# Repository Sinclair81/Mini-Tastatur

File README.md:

# Mini-Tastatur

<!-- markdownlint-disable MD033 -->

<!-- markdownlint-enable MD033 -->

A smal clone of the [Adafruit MacroPad RP2040](https://learn.adafruit.com/adafruit-macropad-rp2040).  

- Raspberry Pi Pico
- I2C Display
- 9 Buttons

[CircuitPython for Raspberry Pi Pico](https://circuitpython.org/board/raspberry_pi_pico)

[MacroPad CircuitPython Library](https://learn.adafruit.com/adafruit-macropad-rp2040/macropad-circuitpython-library)

Extract the zip and navigate to the lib folder found within. Drag the necessary libraries from the zip lib folder to the lib folder on your CIRCUITPY drive.

At a minimum, the following libraries are required to use the MacroPad CircuitPython library. Drag the following files and folders to the lib folder on your CIRCUITPY drive:

adafruit_macropad.mpy - A helper library for using the features of the Adafruit MacroPad.
adafruit_debouncer.mpy - A helper library for debouncing pins. Used to provide a debounced instance of the rotary encoder switch.
adafruit_simple_text_display.mpy - A helper library for easily displaying lines of text on a display.
neopixel.mpy - A CircuitPython driver for NeoPixel LEDs.
adafruit_display_text/ - A library to display text using displayio. Used for the text display functionality of the MacroPad library that allows you easily display lines of text on the built-in display.
adafruit_hid/ - CircuitPython USB HID drivers.
adafruit_midi/ - A CircuitPython helper for encoding/decoding MIDI packets over a MIDI or UART connection
adafruit_ticks.mpy - A helper to work with intervals and deadlines in milliseconds

There is an example included that uses a library that is not required for the MacroPad library to work, but provides a convenient way to layout text in grid. The following library is recommended as well:

adafruit_displayio_layout - A library that includes a grid layout helper.

[MacroPad Basics](https://learn.adafruit.com/adafruit-macropad-rp2040/macropad-basics)  

[MacroPad Display Text](https://learn.adafruit.com/adafruit-macropad-rp2040/macropad-display-text)  

[MacroPad Keyboard and Mouse](https://learn.adafruit.com/adafruit-macropad-rp2040/macropad-keyboard-and-mouse)  

[Arduino IDE Setup](https://learn.adafruit.com/adafruit-macropad-rp2040/arduino-ide-setup)  

[MacroPad Arduino Example](https://learn.adafruit.com/adafruit-macropad-rp2040/arduino)  

Name                  | Pin
--------------------- | ---------------------
Button / Boot select  | GPIO0 / TP6  
Button 1              | GPIO1  
Button 2              | GPIO2  
Button 3              | GPIO3  
Button 4              | GPIO4  
Button 5              | GPIO5  
Button 6              | GPIO6  
Button 7              | GPIO7  
Button 8              | GPIO8  
Button 9              | GPIO9  
Rotary Encoder A      | GPIO17  
Rotary Encoder B      | GPIO18  
Neopixel (9)          | GPIO19  
Display SDA           | GPIO20  
Display SCL           | GPIO21  
Reset                 | RUN

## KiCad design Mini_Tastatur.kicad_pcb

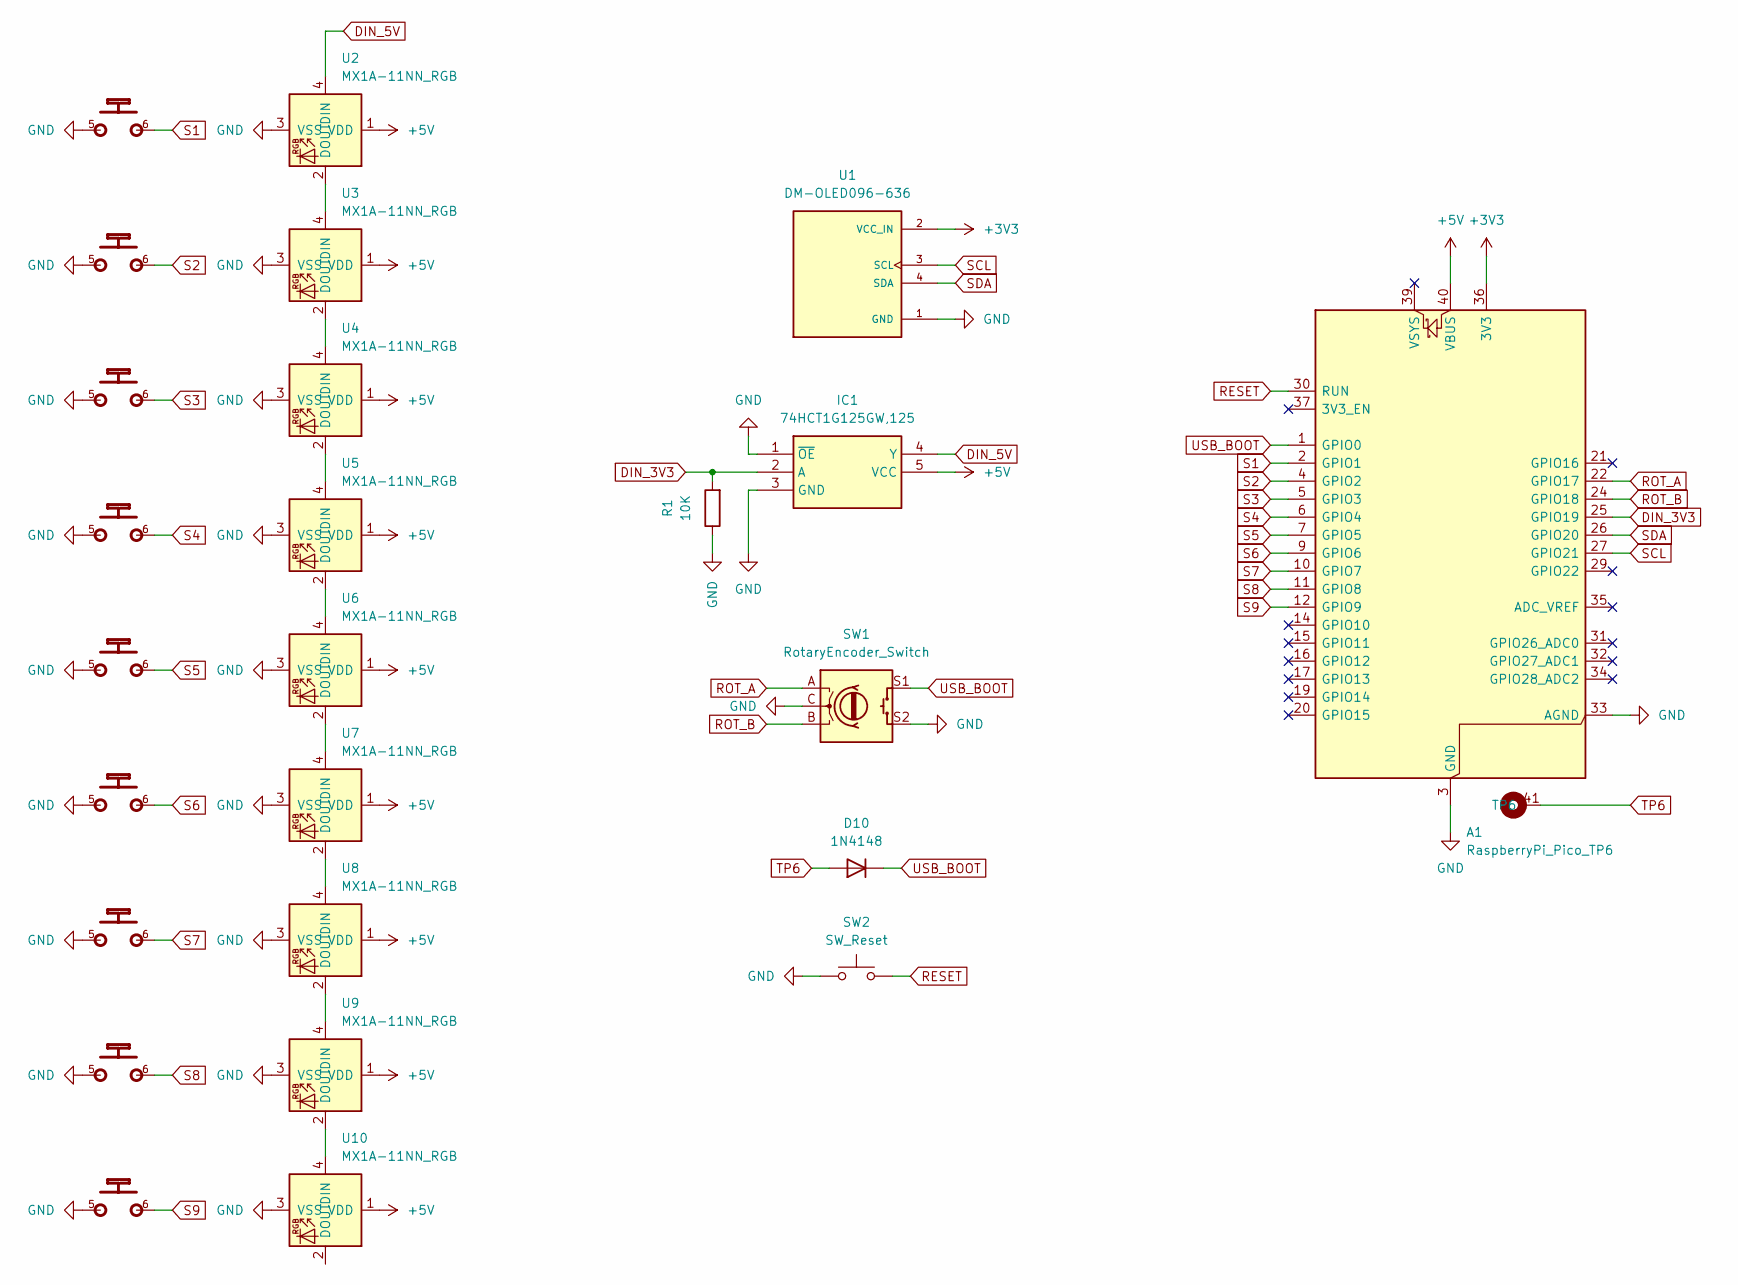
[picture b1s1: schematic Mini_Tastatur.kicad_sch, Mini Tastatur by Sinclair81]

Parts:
A1: RaspberryPi_Pico_TP6; RaspberryPi_Pico_Common_SMD_TP6
D10: 1N4148; D_SOD-523
IC1: 74HCT1G125GW,125; SOT65P212X110-5N; Mouser Part Number 771-74HCT1G125GW-G
R1: 10K; R_0603_1608Metric
SW1: RotaryEncoder_Switch; RotaryEncoder_Alps_EC11E-Switch_Vertical_H20mm
SW2: SW_Reset; SW_Push_1P1T_NO_E-Switch_TL3301NxxxxxG
U1: DM-OLED096-636; MODULE_DM-OLED096-636; PARTREV 2018-09-10
U2, U3, U4, U5, U6, U7, U8, U9, U10: MX1A-11NN_RGB; CHERRY_MX1A-11NN_SWITCH_RGB

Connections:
+3V3: A1.36 (3V3), U1.2 (VCC_IN)
+5V: A1.40 (VBUS), IC1.5 (VCC), U2.1 (VDD), U3.1 (VDD), U4.1 (VDD), U5.1 (VDD), U6.1 (VDD), U7.1 (VDD), U8.1 (VDD), U9.1 (VDD), U10.1 (VDD)
DIN_3V3: A1.25 (GPIO19), IC1.2 (A), R1.2
DIN_5V: IC1.4 (Y), U2.4 (DIN)
GND: A1.3 (GND), A1.8 (GND), A1.13 (GND), A1.18 (GND), A1.23 (GND), A1.28 (GND), A1.33 (AGND), A1.38 (GND), IC1.1 (~OE), IC1.3 (GND), R1.1, SW1.C, SW1.S2, SW2.1, U1.1 (GND), U2.3 (VSS), U2.5, U3.3 (VSS), U3.5, U4.3 (VSS), U4.5, U5.3 (VSS), U5.5, U6.3 (VSS), U6.5, U7.3 (VSS), U7.5, U8.3 (VSS), U8.5, U9.3 (VSS), U9.5, U10.3 (VSS), U10.5
unnamed: U2.2 (DOUT), U3.4 (DIN)
unnamed: U3.2 (DOUT), U4.4 (DIN)
unnamed: U4.2 (DOUT), U5.4 (DIN)
unnamed: U5.2 (DOUT), U6.4 (DIN)
unnamed: U6.2 (DOUT), U7.4 (DIN)
unnamed: U7.2 (DOUT), U8.4 (DIN)
unnamed: U8.2 (DOUT), U9.4 (DIN)
unnamed: U9.2 (DOUT), U10.4 (DIN)
RESET: A1.30 (RUN), SW2.2
ROT_A: A1.22 (GPIO17), SW1.A
ROT_B: A1.24 (GPIO18), SW1.B
S1: A1.2 (GPIO1), U2.6
S2: A1.4 (GPIO2), U3.6
S3: A1.5 (GPIO3), U4.6
S4: A1.6 (GPIO4), U5.6
S5: A1.7 (GPIO5), U6.6
S6: A1.9 (GPIO6), U7.6
S7: A1.10 (GPIO7), U8.6
S8: A1.11 (GPIO8), U9.6
S9: A1.12 (GPIO9), U10.6
SCL: A1.27 (GPIO21), U1.3 (SCL)
SDA: A1.26 (GPIO20), U1.4 (SDA)
TP6: A1.41 (TP6), D10.2 (A)
USB_BOOT: A1.1 (GPIO0), D10.1 (K), SW1.S1

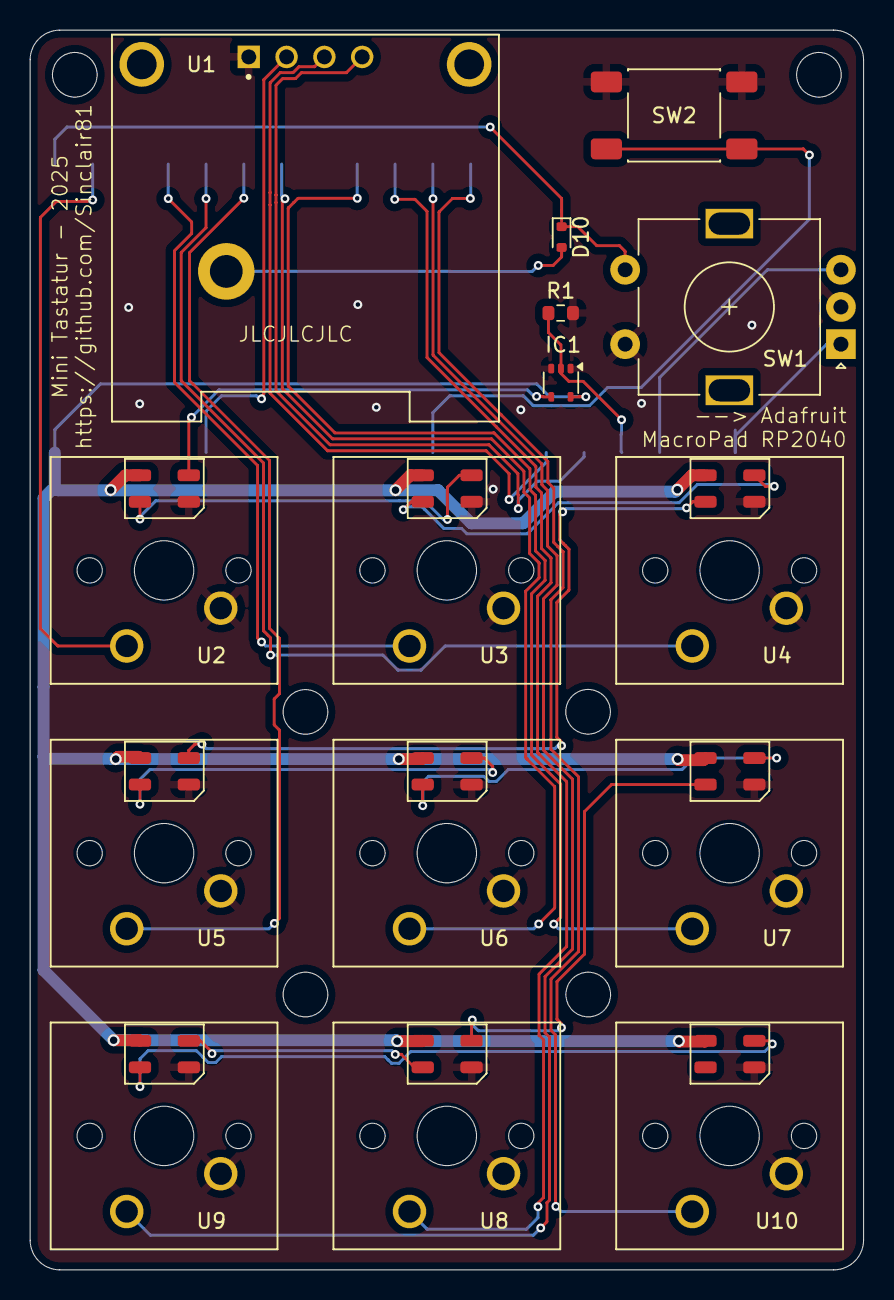
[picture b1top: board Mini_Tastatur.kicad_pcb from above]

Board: 2 copper layers, 56.0 x 83.3 mm, 16 parts (1 on the bottom side), 29 nets.

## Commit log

2025-09-19 3d print
2025-09-20 STL v14
2025-09-20 STL Images
2025-09-20 test code
2025-10-02 Add Test's and Lib's
2025-10-02 config
